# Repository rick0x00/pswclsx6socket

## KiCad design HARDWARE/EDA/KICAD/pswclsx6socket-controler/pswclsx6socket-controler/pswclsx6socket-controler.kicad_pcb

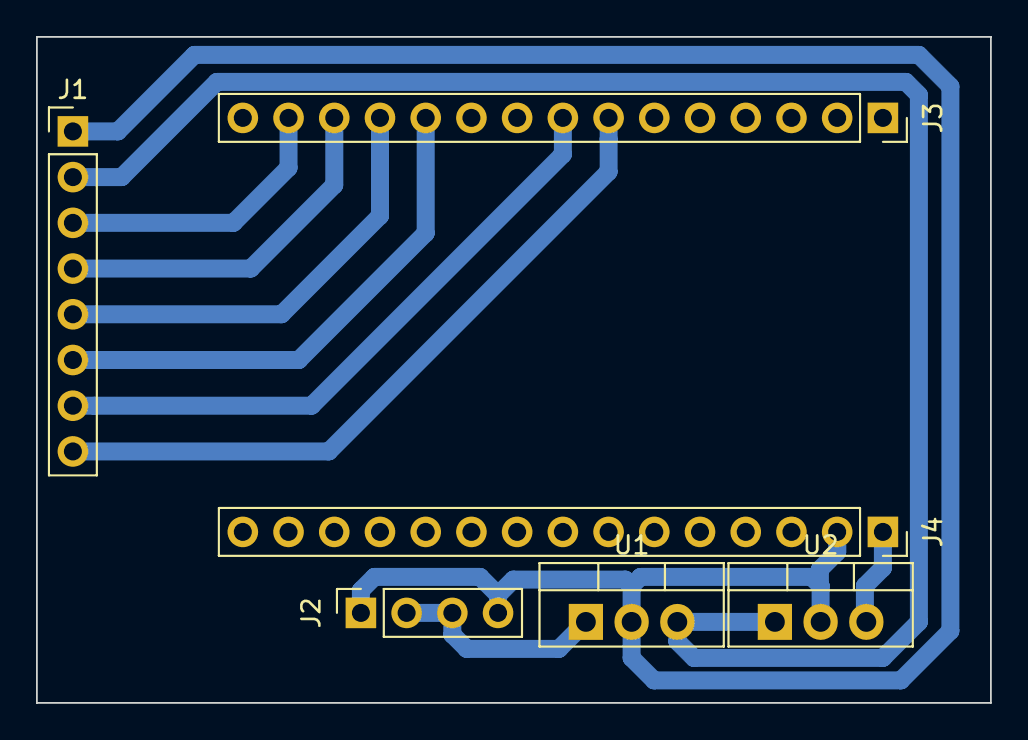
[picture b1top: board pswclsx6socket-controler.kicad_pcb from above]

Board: 2 copper layers, 53.0 x 37.0 mm, 6 parts (0 on the bottom side), 10 nets.

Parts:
J1: pswcls-master; PinHeader_1x08_P2.54mm_Vertical
J2: PWR-12VA; PinSocket_1x04_P2.54mm_Vertical
J3: NODE-MCU-L; PinSocket_1x15_P2.54mm_Vertical
J4: NODE-MCU-R; PinSocket_1x15_P2.54mm_Vertical
U1: LM7812_TO220; TO-220-3_Vertical
U2: LM7805_TO220; TO-220-3_Vertical

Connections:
+5V: J4.1, U2.3
+12VA: J2.2, J2.3, U1.1
GND: J1.1, J2.1, J2.4, J4.2, U1.2, U2.2
vcc_relay-master: J1.2, U1.3, U2.1
vll_relay-1: J1.3, J3.14
vll_relay-2: J1.4, J3.13
vll_relay-3: J1.5, J3.12
vll_relay-4: J1.6, J3.11
vll_relay-5: J1.7, J3.8
vll_relay-6: J1.8, J3.7

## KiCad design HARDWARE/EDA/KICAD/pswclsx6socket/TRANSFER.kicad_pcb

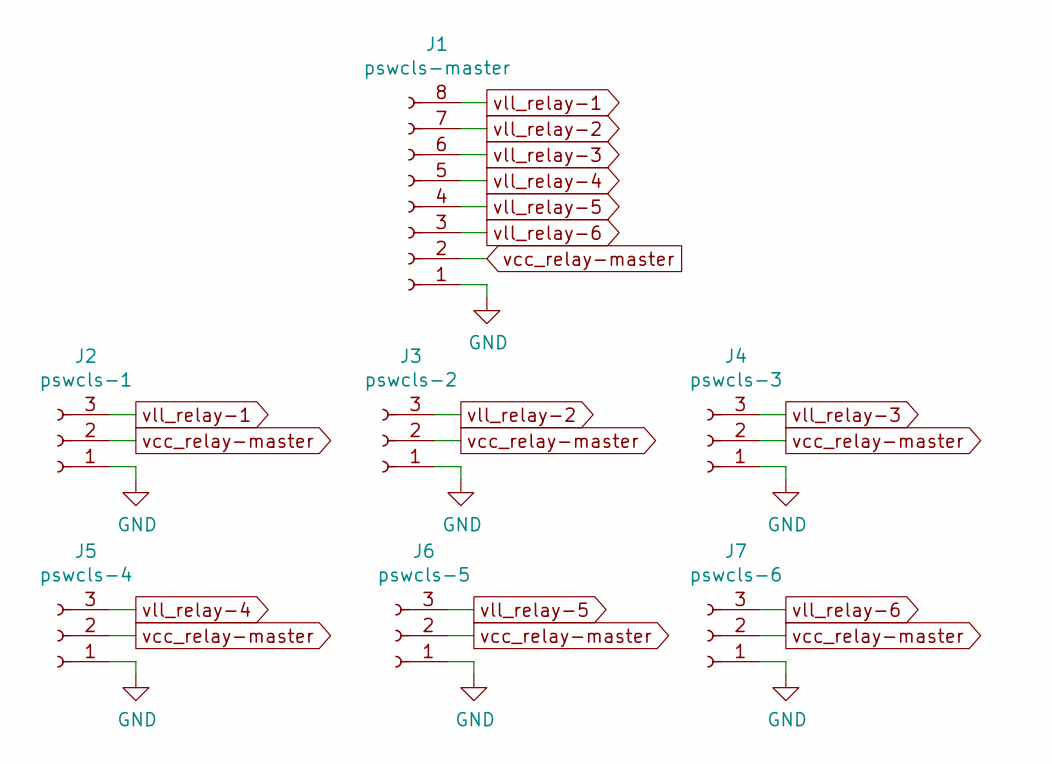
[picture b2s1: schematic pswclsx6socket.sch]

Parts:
J1: pswcls-master; PinSocket_1x08_P2.54mm_Vertical
J2: pswcls-1; PinSocket_1x03_P2.54mm_Vertical
J3: pswcls-2; PinSocket_1x03_P2.54mm_Vertical
J4: pswcls-3; PinSocket_1x03_P2.54mm_Vertical
J5: pswcls-4; PinSocket_1x03_P2.54mm_Vertical
J6: pswcls-5; PinSocket_1x03_P2.54mm_Vertical
J7: pswcls-6; PinSocket_1x03_P2.54mm_Vertical

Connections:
GND: J1.1, J2.1, J3.1, J4.1, J5.1, J6.1, J7.1
vcc_relay-master: J1.2, J2.2, J3.2, J4.2, J5.2, J6.2, J7.2
vll_relay-1: J1.8, J2.3
vll_relay-2: J1.7, J3.3
vll_relay-3: J1.6, J4.3
vll_relay-4: J1.5, J5.3
vll_relay-5: J1.4, J6.3
vll_relay-6: J1.3, J7.3

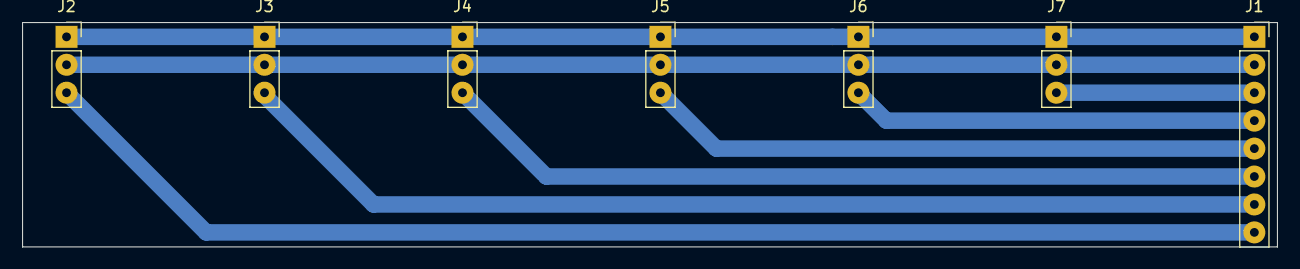
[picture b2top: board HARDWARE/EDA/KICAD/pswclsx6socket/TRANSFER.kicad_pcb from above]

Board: 2 copper layers, 114.1 x 20.4 mm, 7 parts (0 on the bottom side), 8 nets.

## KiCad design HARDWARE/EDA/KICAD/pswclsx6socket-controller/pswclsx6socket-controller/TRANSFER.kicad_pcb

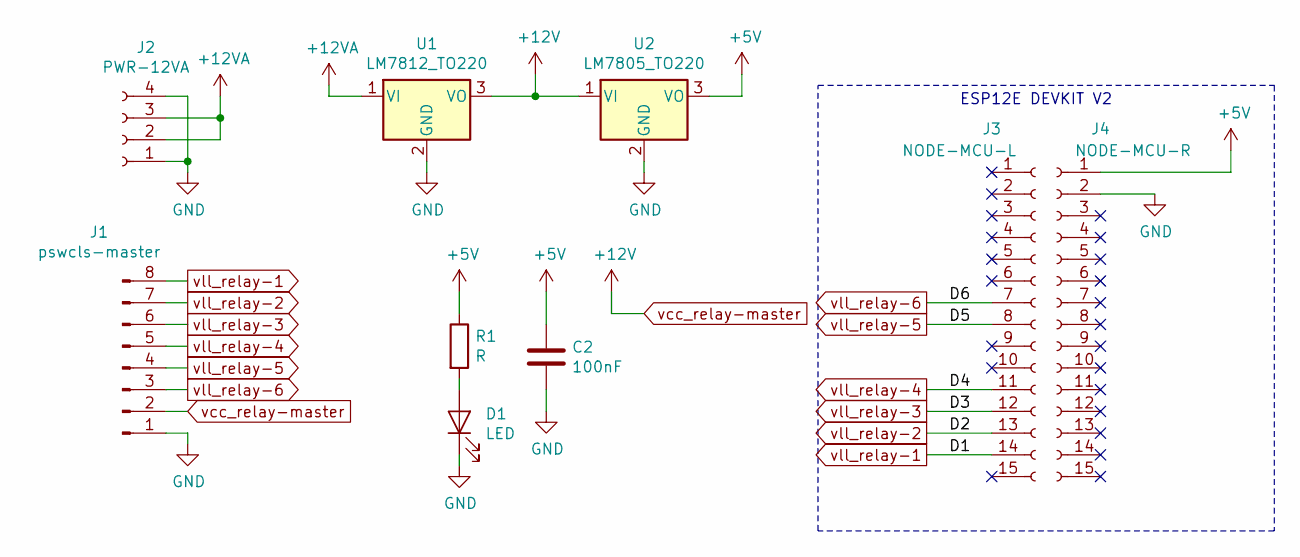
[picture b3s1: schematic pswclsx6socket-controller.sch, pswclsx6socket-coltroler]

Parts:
C2: 100nF; C_Rect_L7.0mm_W2.0mm_P5.00mm
D1: LED; LED_D5.0mm
J1: pswcls-master; PinHeader_1x08_P2.54mm_Horizontal
J2: PWR-12VA; PinSocket_1x04_P2.54mm_Vertical
J3: NODE-MCU-L; PinSocket_1x15_P2.54mm_Vertical
J4: NODE-MCU-R; PinSocket_1x15_P2.54mm_Vertical
R1: R; R_Axial_DIN0207_L6.3mm_D2.5mm_P7.62mm_Horizontal
U1: LM7812_TO220; TO-220-3_Vertical
U2: LM7805_TO220; TO-220-3_Vertical

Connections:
+5V: C2.1, J4.1, R1.1, U2.3 (VO)
+12VA: J2.2, J2.3, U1.1 (VI)
GND: C2.2, D1.1 (K), J1.1, J2.1, J2.4, J4.2, U1.2 (GND), U2.2 (GND)
unnamed: D1.2 (A), R1.2
vcc_relay-master: J1.2, U1.3 (VO), U2.1 (VI)
vll_relay-1: J1.8, J3.14
vll_relay-2: J1.7, J3.13
vll_relay-3: J1.6, J3.12
vll_relay-4: J1.5, J3.11
vll_relay-5: J1.4, J3.8
vll_relay-6: J1.3, J3.7

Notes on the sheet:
ESP12E DEVKIT V2

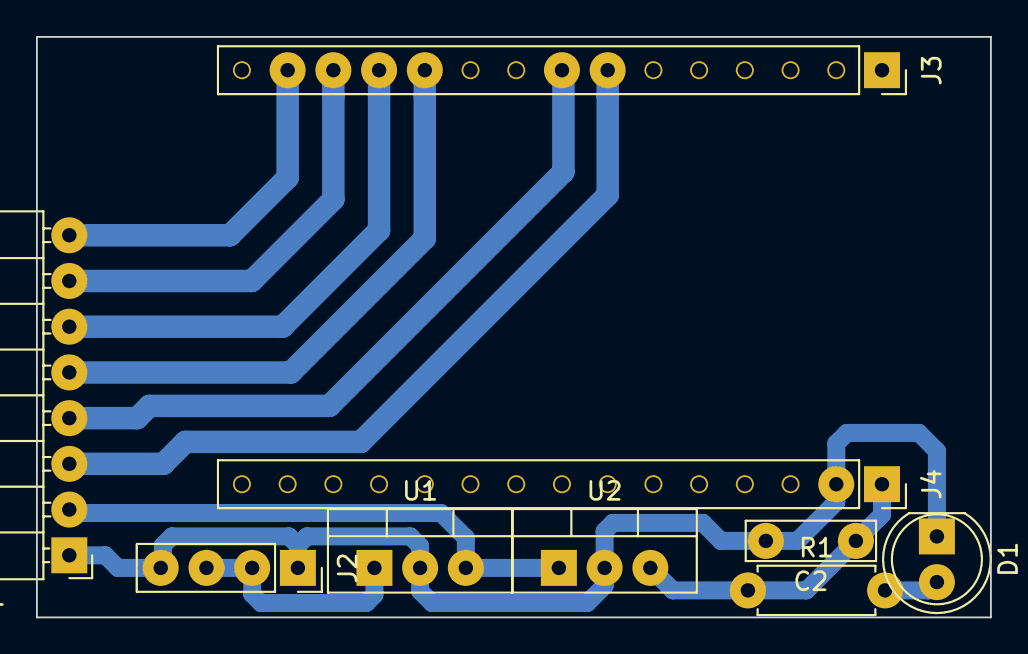
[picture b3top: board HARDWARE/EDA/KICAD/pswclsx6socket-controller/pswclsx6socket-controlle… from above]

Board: 2 copper layers, 53.0 x 32.2 mm, 9 parts (0 on the bottom side), 11 nets.

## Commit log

2022-04-16 finished
2022-04-16 controller added
2022-04-19 complement adjusts
2022-04-20 add image
